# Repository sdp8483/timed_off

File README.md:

# Auto Off Circuit for Low Power AC Devices
For more info: https://samueldperry.com/2021/07/25/modifying-a-boot-dryer/

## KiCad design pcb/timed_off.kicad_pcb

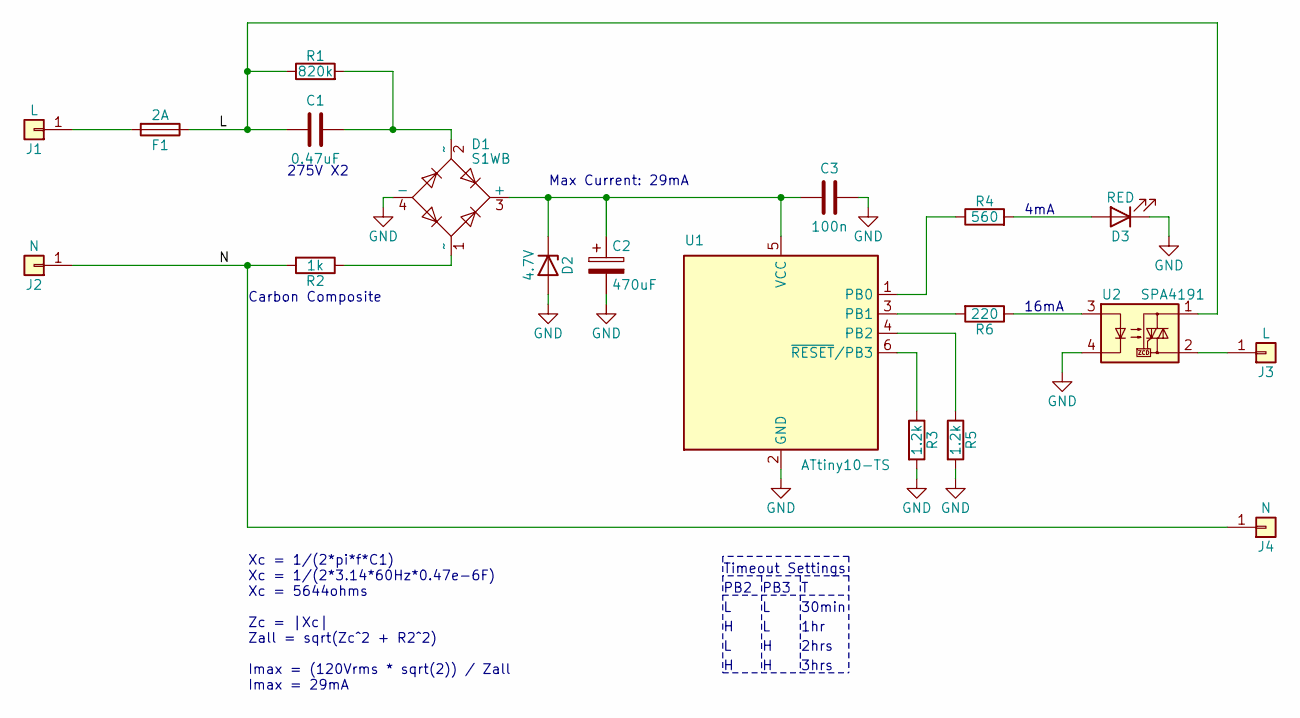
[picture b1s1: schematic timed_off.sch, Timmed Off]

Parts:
C1: 0.47uF; C_Rect_L29.0mm_W11.0mm_P27.50mm_MKT
C2: 470uF; CP_Radial_D8.0mm_P3.80mm
C3: 100n; C_Disc_D6.0mm_W2.5mm_P5.00mm
D1: S1WB
D2: 4.7V; D_DO-35_SOD27_P7.62mm_Horizontal
D3: RED; LED_D5.0mm
F1: 2A; R_Axial_DIN0309_L9.0mm_D3.2mm_P5.08mm_Vertical
J1, J3: L; TestPoint_Plated_Hole_D2.0mm
J2, J4: N; TestPoint_Plated_Hole_D2.0mm
R1: 820k; R_Axial_DIN0207_L6.3mm_D2.5mm_P10.16mm_Horizontal
R2: 1k; R_Axial_DIN0411_L9.9mm_D3.6mm_P7.62mm_Vertical
R3, R5: 1.2k; R_Axial_DIN0207_L6.3mm_D2.5mm_P10.16mm_Horizontal
R4: 560; R_Axial_DIN0207_L6.3mm_D2.5mm_P10.16mm_Horizontal
R6: 220; R_Axial_DIN0207_L6.3mm_D2.5mm_P10.16mm_Horizontal
U1: ATtiny10-TS; SOT-23-6
U2: SPA4191

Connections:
/L: C1.2, F1.1, R1.1, U2.1
/N: J2.1, J4.1, R2.2
GND: C2.2, C3.1, D1.4 (-), D2.2 (A), D3.1 (K), R3.2, R5.2, U1.2 (GND), U2.4
unnamed: C1.1, D1.2 (~~), R1.2
unnamed: C2.1, C3.2, D1.3 (+), D2.1 (K), U1.5 (VCC)
unnamed: D1.1 (~~), R2.1
unnamed: D3.2 (A), R4.2
unnamed: F1.2, J1.1
unnamed: J3.1, U2.2
unnamed: R3.1, U1.6 (~RESET~/PB3)
unnamed: R4.1, U1.1 (PB0)
unnamed: R5.1, U1.4 (PB2)
unnamed: R6.1, U2.3
unnamed: R6.2, U1.3 (PB1)

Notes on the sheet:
16mA
PB2
PB3
30min
1hr
2hrs
3hrs
Timeout Settings
275V X2
Carbon Composite
Max Current: 29mA
Xc = 1/(2*pi*f*C1) Xc = 1/(2*3.14*60Hz*0.47e-6F) Xc = 5644ohms Zc = |Xc| Zall = sqrt(Zc^2 + R2^2) Imax = (120Vrms * sqrt(2)) / Zall Imax = 29mA
4mA

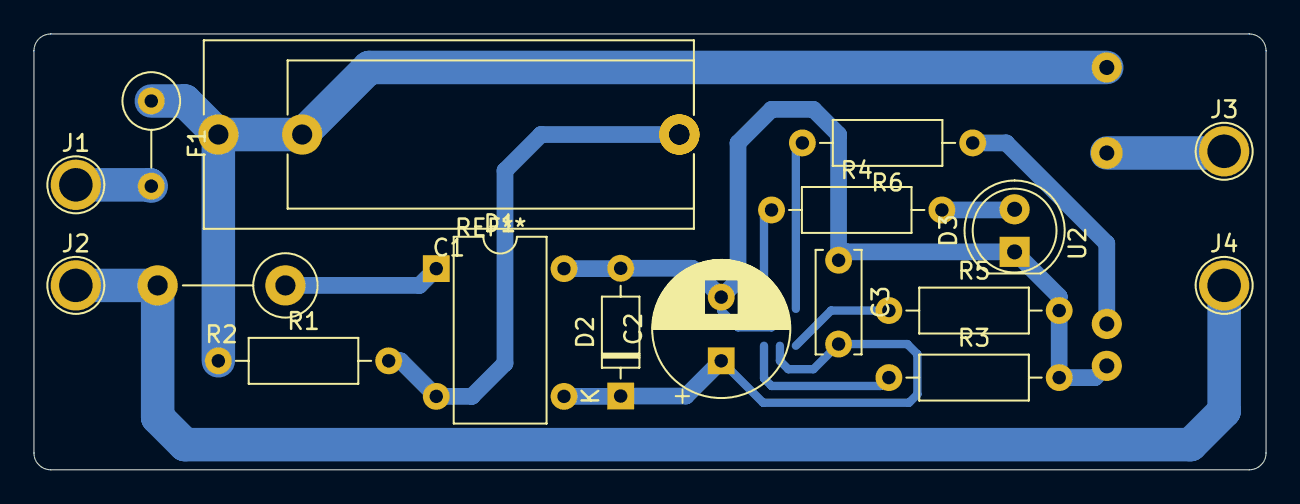
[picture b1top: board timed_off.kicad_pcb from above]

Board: 2 copper layers, 73.5 x 26.0 mm, 19 parts (1 on the bottom side), 14 nets.

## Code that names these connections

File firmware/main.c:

/* Timed Power Off
 *  turn off SSR after set amount of time after first power on
 * 
 * Clk: 1MHz
 * Simple Connection Diagram
 *       ATTINY10
 *       ---------
 *   3v | 5  1 PB0| -> SSR
 *   GND| 2  3 PB1| -> LED
 *      |    4 PB2| <- Resistor
 *      |    6 PB3| <- Resistor
 *       ---------
 *        SOT23-6
 * write fuse:
 *      avrdude -c usbasp -p t10 -U fuse:w:0xFE:m
 * 
 * verify fuse:
 *      avrdude -c usbasp -p t10 -t
 *      read fuse
 *      q
 */

#define F_CPU 1000000UL     /* for delay functions */

#include <stdint.h>
#include <avr/io.h>
#include <util/delay.h>
#include <avr/sleep.h>
#include <avr/interrupt.h>

#include "main.h"

#define DELAY_ON_START_ms   5000    /* delay before turning on SSR on first power */

/* timeout settings */
#define TIMEOUT_0           30      /* timeout after X minutes, option 0 */
#define TIMEOUT_1           60      /* timeout after X minutes, option 1 */
#define TIMEOUT_2           120     /* timeout after X minutes, option 2 */
#define TIMEOUT_3           180     /* timeout after X minutes, option 3 */
uint8_t t_array[] = {TIMEOUT_0, TIMEOUT_1, TIMEOUT_2, TIMEOUT_3};

/* Timer0 60s Tick */
#define TIMER_PRELOAD   (58594)     /* with prescaler of 1024 on Timer0, 58,594 is ~60s when sys clock is 1MHz */
//#define TIMER_PRELOAD   (7500)      /* with a prescaler of 1024 on Timer0, 7,500 is ~60s when sys clock is 128kHz */

volatile uint8_t count = 0;         /* timer0 tick count */

/* Function Prototypes */
void enableTimer0(void);
void disableTimer0(void);

int main(void) {
    /* set PB0 and PB1 as output */
    DDRB |= (BIT0 + BIT1);

    /* set PB2 and PB3 as input, pullups */
    DDRB &= ~(BIT2 + BIT3);
    PUEB |= (BIT2 + BIT3);

    /* read PB2 and PB3 to get the timout setting */
    uint8_t timeout = t_array[(PINB & (BIT2 + BIT3)) >> 2];

    /* wait before enabling SSR to lessen current inrush */
    _delay_ms(DELAY_ON_START_ms);

    /* enable 60s timer */
    enableTimer0();
    sei();

    /* enable SSR and LED */
    PORTB |= (BIT0 + BIT1);

    /* set sleep mode */
    set_sleep_mode(SLEEP_MODE_IDLE);
    
    while(timeout > count) {
        sleep_enable();     /* enable sleep */
        sleep_cpu();        /* go to sleep */
        sleep_disable();    /* wake from sleep here on timer0 interrupt */
    }

    /* disable SSR and LED */
    PORTB &= ~(BIT0 + BIT1);

    /* disable timer0 */
    disableTimer0();
    
    while(1) {
        /* deep sleep with no interrupt */
        set_sleep_mode(SLEEP_MODE_PWR_DOWN);
        sleep_enable();     /* enable sleep */
        sleep_cpu();        /* go to sleep */
    }
}

/* enable timer0 to trigger ISR for auto power off */
void enableTimer0(void) {
    TCCR0A = 0;                         /* OC0A/OC0B disconnected ie no output on pins*/
    TCCR0B = (BIT3 + BIT2 + BIT0);      /* clear timer on compare,  timer prescaler is 1024*/

    OCR0AH = (TIMER_PRELOAD >> 8);      /* set output compare register high byte */
    OCR0AL = (TIMER_PRELOAD & 0xFF);    /* set output compare register low byte */

    TCNT0H = 0;                         /* set timer count to zero */
    TCNT0L = 0;

    TIMSK0 |= (1 << OCIE0A);            /* enable ISR on Output compare A match */
}

/* disable timer0 when sleeping to save power */
void disableTimer0(void) {
    TCCR0A = 0;
    TCCR0B &= ~(BIT2 + BIT1 + BIT0);    /* set timer prescaler to 0 to disable */

    TIMSK0 &= ~(1 << OCIE0A);           /* disable ISR */
}

ISR(TIM0_COMPA_vect) {
    count++;
}

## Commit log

2021-07-13 init commit
2021-07-13 add timer0 init code and start dev
2021-07-13 add SPA4191 datasheet
2021-07-13 add footprints
2021-07-15 fix bridge footprint, add second dropper cap footprint
2021-07-15 create gcode
2021-07-17 increase insert hole size, fix cord orientation
2021-07-18 more cord grip
2021-07-25 export for 3d printing
2021-07-25 assembled pcb images
